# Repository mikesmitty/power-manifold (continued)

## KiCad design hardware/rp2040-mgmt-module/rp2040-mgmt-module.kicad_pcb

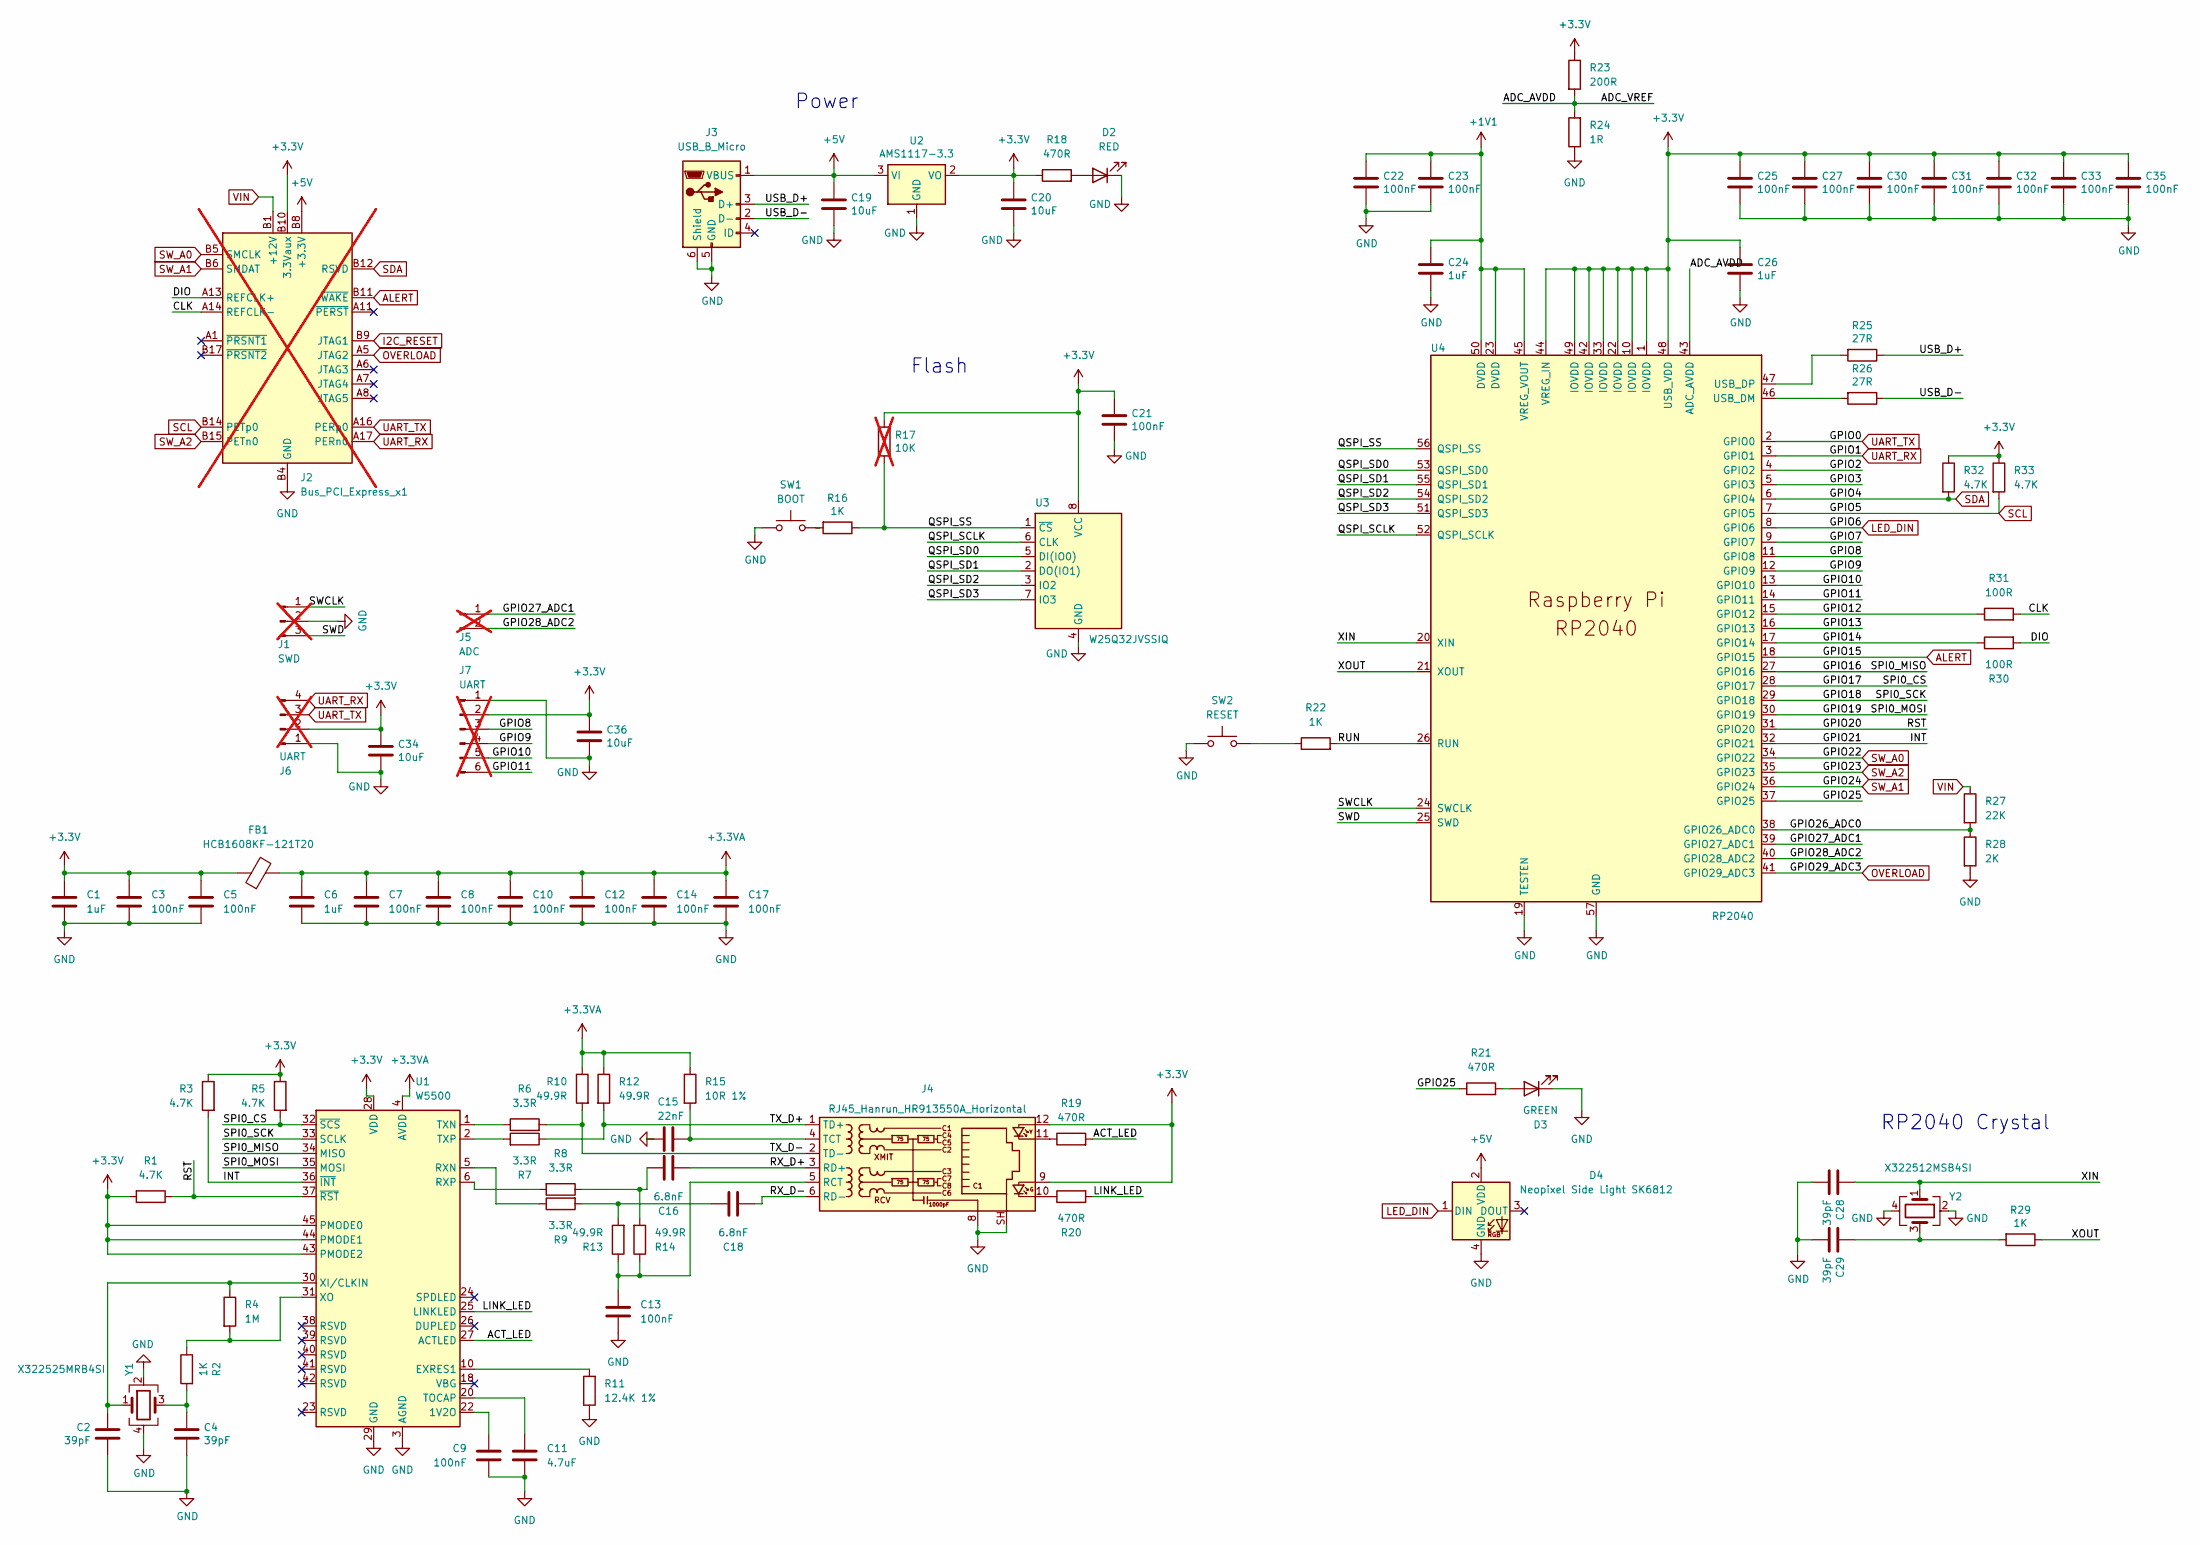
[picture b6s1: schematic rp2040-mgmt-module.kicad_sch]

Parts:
C1, C6, C24, C26: 1uF; C_0402_1005Metric; LCSC C52923
C2, C4, C28, C29: 39pF; C_0402_1005Metric; LCSC C342946
C3, C5, C7, C8, C9, C10, C12, C13, C14, C17, C21, C22, C23, C25, C27, C30, C31, C32, C33, C35: 100nF; C_0402_1005Metric; LCSC C1525
C11: 4.7uF; C_0402_1005Metric; LCSC C23733
C15: 22nF; C_0402_1005Metric; LCSC C1532
C16, C18: 6.8nF; C_0402_1005Metric; LCSC C1542
C19, C20, C34, C36: 10uF; C_0402_1005Metric; LCSC C15525
D2: RED; LED_0603_1608Metric; LCSC C2286
D3: GREEN; LED_0603_1608Metric; LCSC C965804
D4: Neopixel Side Light SK6812; LED_Neopixel_Side_Light_SK6812; LCSC C5378721
FB1: HCB1608KF-121T20; L_0603_1608Metric; LCSC C127301
J1: SWD; PinSocket_1x03_P2.54mm_Vertical; not fitted
J2: Bus_PCI_Express_x1; BUS_PCIexpress_x1; not fitted
J3: USB_B_Micro; USB_Micro-B_XKB_U254-051T-4BH83-F1S; LCSC C319160
J4: RJ45_Hanrun_HR913550A_Horizontal; RJ45_Hanrun_HR911105A_Horizontal; LCSC C163507
J5: ADC; PinSocket_1x02_P2.54mm_Vertical; not fitted
J6: UART; PinHeader_1x04_P2.54mm_Vertical; not fitted
J7: UART; PinHeader_1x06_P2.54mm_Vertical; not fitted
R1, R3, R5, R32, R33: 4.7K; R_0402_1005Metric; LCSC C25900
R2, R16, R22, R29: 1K; R_0402_1005Metric; LCSC C11702
R4: 1M; R_0402_1005Metric; LCSC C26083
R6, R7, R8, R9: 3.3R; R_0402_1005Metric; LCSC C270612
R10, R12, R13, R14: 49.9R; R_0402_1005Metric; LCSC C25120
R11: 12.4K 1%; R_0402_1005Metric; LCSC C11692
R15: 10R 1%; R_0402_1005Metric; LCSC C25077
R17: 10K; R_0402_1005Metric; not fitted
R18, R19, R20, R21: 470R; R_0402_1005Metric; LCSC C25117
R23: 200R; R_0402_1005Metric; LCSC C25087
R24: 1R; R_0402_1005Metric; LCSC C25086
R25, R26: 27R; R_0402_1005Metric; LCSC C25100
R27: 22K; R_0402_1005Metric; LCSC C25768
R28: 2K; R_0402_1005Metric; LCSC C4109
R30, R31: 100R; R_0402_1005Metric; LCSC C25076
SW1: BOOT; XKB_TS-1101_SWITCH; LCSC C318938
SW2: RESET; XKB_TS-1101_SWITCH; LCSC C318938
U1: W5500; LQFP-48_7x7mm_P0.5mm; LCSC C32843
U2: AMS1117-3.3; SOT-223-3_TabPin2; LCSC C6186
U3: W25Q32JVSSIQ; SOIC-8_5.23x5.23mm_P1.27mm; LCSC C179173
U4: RP2040; QFN-56-1EP_7x7mm_P0.4mm_EP3.2x3.2mm; LCSC C2040
Y1: X322525MRB4SI; Crystal_SMD_3225-4Pin_3.2x2.5mm; LCSC C70593
Y2: X322512MSB4SI; Crystal_SMD_3225-4Pin_3.2x2.5mm; LCSC C9002

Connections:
+1V1: C22.1, C23.1, C24.1, U4.23 (DVDD), U4.45 (VREG_VOUT), U4.50 (DVDD)
+3.3V: C1.1, C3.1, C5.1, C20.1, C21.1, C25.1, C26.1, C27.1, C30.1, C31.1, C32.1, C33.1, C34.1, C35.1, C36.1, FB1.1, J2.B10 (3.3Vaux), J4.9, J4.12, J6.2, J7.2, R1.2, R3.1, R5.1, R17.1, R18.1, R23.1, R32.1, R33.1, U1.28 (VDD), U1.43 (PMODE2), U1.44 (PMODE1), U1.45 (PMODE0), U2.2 (VO), U3.8 (VCC), U4.1 (IOVDD), U4.10 (IOVDD), U4.22 (IOVDD), U4.33 (IOVDD), U4.42 (IOVDD), U4.44 (VREG_IN), U4.48 (USB_VDD), U4.49 (IOVDD)
+3.3VA: C6.1, C7.1, C8.1, C10.1, C12.1, C14.1, C17.1, FB1.2, R10.1, R12.1, R15.1, U1.4 (AVDD), U1.8 (AVDD), U1.11 (AVDD), U1.15 (AVDD), U1.17 (AVDD), U1.21 (AVDD)
+5V: C19.1, D4.2 (VDD), J2.A9 (+3.3V), J2.A10 (+3.3V), J2.B8 (+3.3V), J3.1 (VBUS), U2.3 (VI)
/ACT_LED: R19.2, U1.27 (ACTLED)
/ADC_AVDD: R23.2, R24.2, U4.43 (ADC_AVDD)
/CLK: J2.A14 (REFCLK-), R31.2
/DIO: J2.A13 (REFCLK+), R30.2
/GPIO2: U4.4 (GPIO2)
/GPIO3: U4.5 (GPIO3)
/GPIO7: U4.9 (GPIO7)
/GPIO8: J7.3, U4.11 (GPIO8)
/GPIO9: J7.4, U4.12 (GPIO9)
/GPIO10: J7.5, U4.13 (GPIO10)
/GPIO11: J7.6, U4.14 (GPIO11)
/GPIO12: R31.1, U4.15 (GPIO12)
/GPIO13: U4.16 (GPIO13)
/GPIO14: R30.1, U4.17 (GPIO14)
/GPIO16: U1.34 (MISO), U4.27 (GPIO16)
/GPIO17: R5.2, U1.32 (~SCS), U4.28 (GPIO17)
/GPIO18: U1.33 (SCLK), U4.29 (GPIO18)
/GPIO19: U1.35 (MOSI), U4.30 (GPIO19)
/GPIO20: R1.1, U1.37 (~RST), U4.31 (GPIO20)
/GPIO21: R3.2, U1.36 (~INT), U4.32 (GPIO21)
/GPIO25: R21.1, U4.37 (GPIO25)
/GPIO26_ADC0: R27.2, R28.1, U4.38 (GPIO26_ADC0)
/GPIO27_ADC1: J5.1, U4.39 (GPIO27_ADC1)
/GPIO28_ADC2: J5.2, U4.40 (GPIO28_ADC2)
/LINK_LED: R20.2, U1.25 (LINKLED)
/QSPI_SCLK: U3.6 (CLK), U4.52 (QSPI_SCLK)
/QSPI_SD0: U3.5 (DI(IO0)), U4.53 (QSPI_SD0)
/QSPI_SD1: U3.2 (DO(IO1)), U4.55 (QSPI_SD1)
/QSPI_SD2: U3.3 (IO2), U4.54 (QSPI_SD2)
/QSPI_SD3: U3.7 (IO3), U4.51 (QSPI_SD3)
/QSPI_SS: R16.1, R17.2, U3.1 (~CS), U4.56 (QSPI_SS)
/RUN: R22.2, U4.26 (RUN)
/RX_D+: C16.2, J4.3 (RD+)
/RX_D-: C18.2, J4.6 (RD-)
/SWCLK: J1.1, U4.24 (SWCLK)
/SWD: J1.3, U4.25 (SWD)
/TX_D+: J4.1 (TD+), R7.1, R12.2
/TX_D-: J4.2 (TD-), R6.2, R10.2
/USB_D+: J3.3 (D+), R25.1
/USB_D-: J3.2 (D-), R26.1
/XIN: C28.1, U4.20 (XIN), Y2.1
/XOUT: R29.1, U4.21 (XOUT)
ALERT: J2.B11 (~WAKE), U4.18 (GPIO15)
GND: C1.2, C2.2, C3.2, C4.2, C5.2, C6.2, C7.2, C8.2, C9.2, C10.2, C11.2, C12.2, C13.2, C14.2, C15.1, C17.2, C19.2, C20.2, C21.2, C22.2, C23.2, C24.2, C25.2, C26.2, C27.2, C28.2, C29.2, C30.2, C31.2, C32.2, C33.2, C34.2, C35.2, C36.2, D2.1 (K), D3.1 (K), D4.4 (GND), J1.2, J2.A4 (GND), J2.A12 (GND), J2.A15 (GND), J2.A18 (GND), J2.B4 (GND), J2.B7 (GND), J2.B13 (GND), J2.B16 (GND), J2.B18 (GND), J3.5 (GND), J3.6 (Shield), J4.8, J4.SH, J6.1, J7.1, R11.1, R24.1, R28.2, SW1.1, SW2.1, U1.3 (AGND), U1.9 (AGND), U1.14 (AGND), U1.16 (AGND), U1.19 (AGND), U1.29 (GND), U1.48 (AGND), U2.1 (GND), U3.4 (GND), U4.19 (TESTEN), U4.57 (GND), Y1.2, Y1.4, Y2.2, Y2.4
I2C_RESET: J2.B9 (JTAG1)
LED_DIN: D4.1 (DIN), U4.8 (GPIO6)
unnamed: C4.1, R2.2, Y1.3
unnamed: C16.1, R8.1, R14.2
unnamed: C18.1, R9.2, R13.2
unnamed: C29.1, R29.2, Y2.3
unnamed: D2.2 (A), R18.2
unnamed: D3.2 (A), R21.2
unnamed: J4.10, R20.1
unnamed: J4.11, R19.1
unnamed: C13.1, J4.5 (RCT), R13.1, R14.1
unnamed: C15.2, J4.4 (TCT), R15.2
unnamed: R16.2, SW1.2
unnamed: R22.1, SW2.2
unnamed: C9.1, U1.22 (1V2O)
unnamed: R11.2, U1.10 (EXRES1)
unnamed: R9.1, U1.5 (RXN)
unnamed: R8.2, U1.6 (RXP)
unnamed: C11.1, U1.20 (TOCAP)
unnamed: R6.1, U1.1 (TXN)
unnamed: R7.2, U1.2 (TXP)
unnamed: C2.1, R4.1, U1.30 (XI/CLKIN), Y1.1
unnamed: R2.1, R4.2, U1.31 (XO)
unnamed: R26.2, U4.46 (USB_DM)
unnamed: R25.2, U4.47 (USB_DP)
OVERLOAD: J2.A5 (JTAG2), U4.41 (GPIO29_ADC3)
SCL: J2.B14 (PETp0), R33.2, U4.7 (GPIO5)
SDA: J2.B12 (RSVD), R32.2, U4.6 (GPIO4)
SW_A0: J2.B5 (SMCLK), U4.34 (GPIO22)
SW_A1: J2.B6 (SMDAT), U4.36 (GPIO24)
SW_A2: J2.B15 (PETn0), U4.35 (GPIO23)
UART_RX: J2.A17 (PERn0), J6.4, U4.3 (GPIO1)
UART_TX: J2.A16 (PERp0), J6.3, U4.2 (GPIO0)
VIN: J2.A2 (+12V), J2.A3 (+12V), J2.B1 (+12V), J2.B2 (+12V), J2.B3 (+12V), R27.1

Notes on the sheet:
Power
Flash
RP2040 Crystal

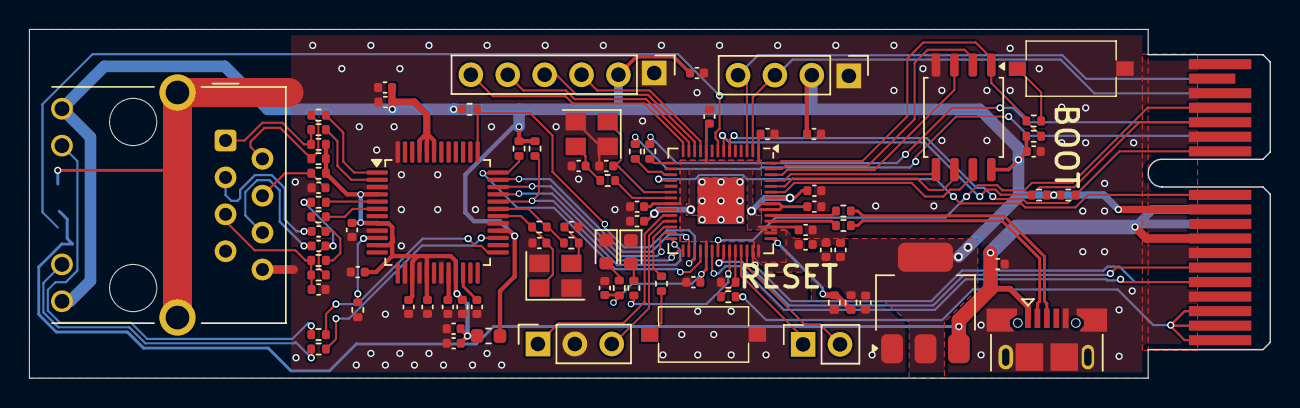
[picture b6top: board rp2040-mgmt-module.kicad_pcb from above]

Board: 2 copper layers, 85.4 x 24.0 mm, 88 parts (1 on the bottom side), 77 nets.

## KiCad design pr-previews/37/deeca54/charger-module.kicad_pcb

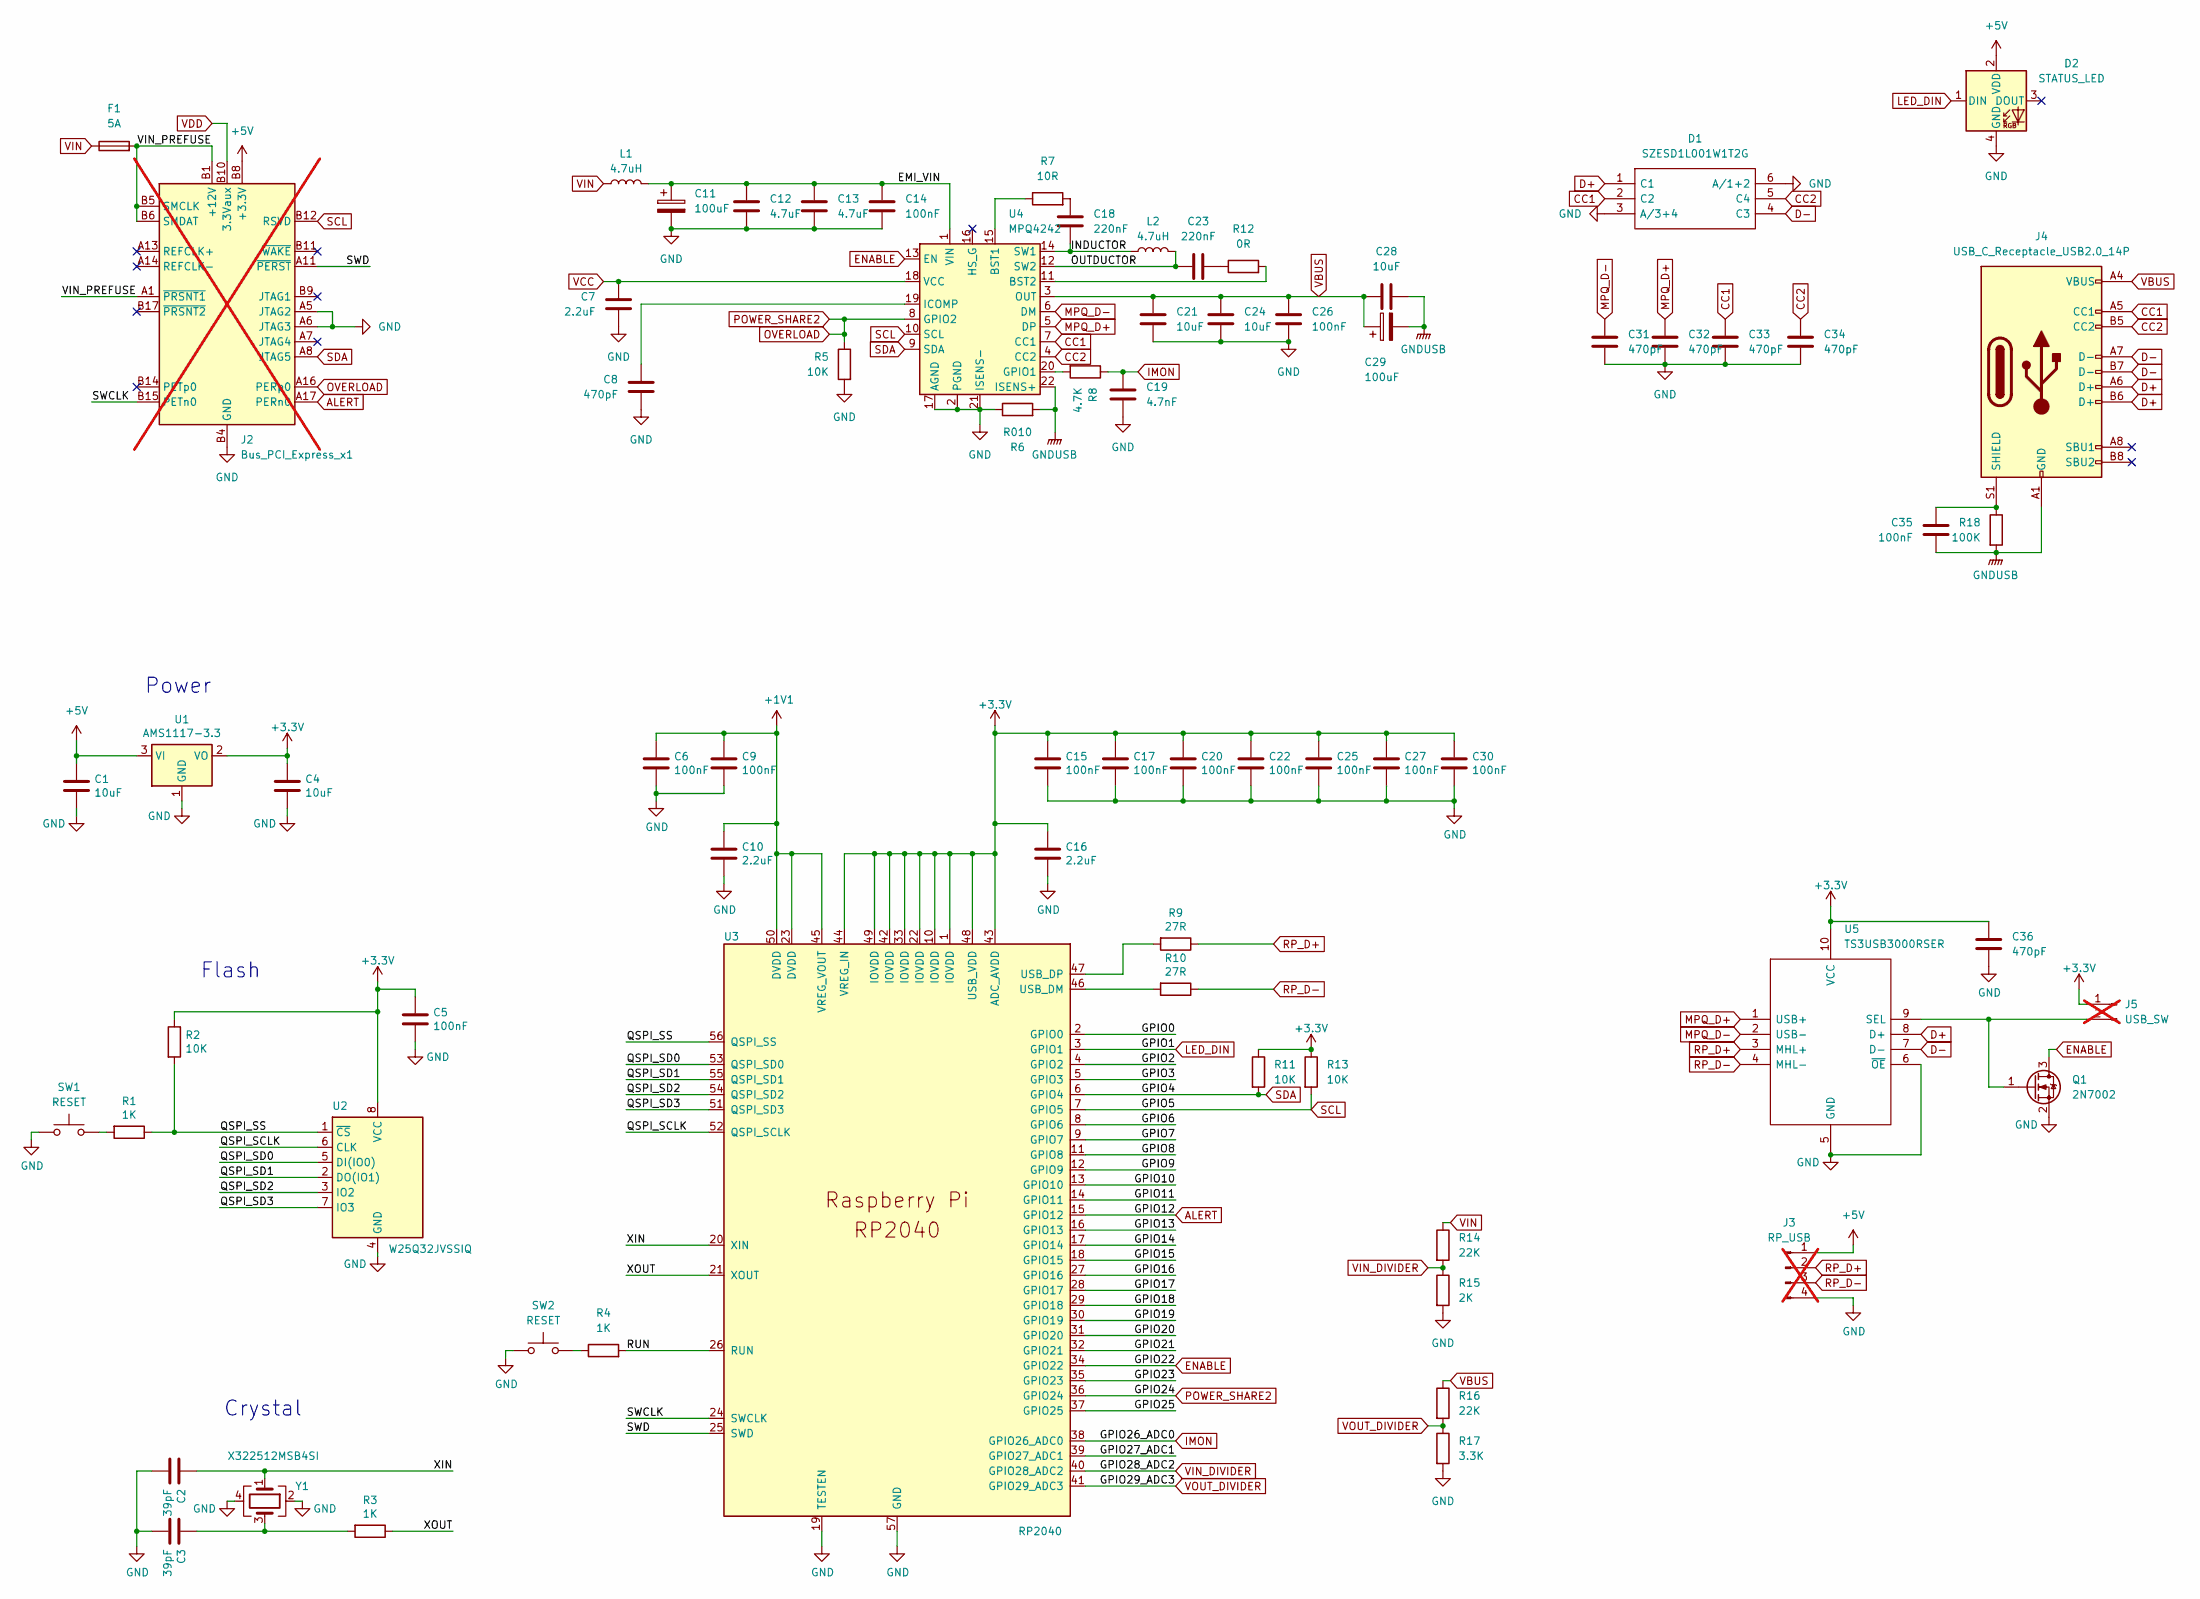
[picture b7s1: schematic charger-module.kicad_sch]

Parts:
C1, C4, C21, C24, C28: 10uF; C_0805_2012Metric; LCSC C15850
C2, C3: 39pF; C_0402_1005Metric; LCSC C106223
C5, C6, C9, C14, C15, C17, C20, C22, C25, C26, C27, C30, C35: 100nF; C_0402_1005Metric; LCSC C1525
C7, C10, C16: 2.2uF; C_0402_1005Metric; LCSC C12530
C8, C31, C32, C33, C34, C36: 470pF; C_0402_1005Metric; LCSC C1537
C11, C29: 100uF; CP_Elec_6.3x7.7; LCSC C3151829
C12, C13: 4.7uF; C_1206_3216Metric; LCSC C29823
C18, C23: 220nF; C_0603_1608Metric; LCSC C21120
C19: 4.7nF; C_0402_1005Metric; LCSC C1538
D1: SZESD1L001W1T2G; SOT65P210X110-6N; Mouser Part Number 863-SZESD1L001W1T2G
D2: STATUS_LED; LED_Neopixel_Side_Light_SK6812; LCSC C5378721
F1: 5A; Fuse_1206_3216Metric; LCSC C553937
J2: Bus_PCI_Express_x1; BUS_PCIexpress_x1; not fitted
J3: RP_USB; PinHeader_1x04_P2.54mm_Vertical; not fitted
J4: USB_C_Receptacle_USB2.0_14P; USB_C_Receptacle_XKB_U262-16XN-4BVC11; LCSC C2931474
J5: USB_SW; PinHeader_1x02_P2.54mm_Vertical; not fitted
L1, L2: 4.7uH; L_Sunlord_MWSA0603S; LCSC C408447
Q1: 2N7002; SOT-23; LCSC C8545
R1, R3, R4: 1K; R_0402_1005Metric; LCSC C11702
R2, R5, R11, R13: 10K; R_0402_1005Metric; LCSC C25744
R6: R010; R_2512_6332Metric; LCSC C127692
R7: 10R; R_0603_1608Metric; LCSC C22859
R8: 4.7K; R_0402_1005Metric; LCSC C25900
R9, R10: 27R; R_0603_1608Metric; LCSC C25190
R12: 0R; R_0603_1608Metric; LCSC C21189
R14, R16: 22K; R_0402_1005Metric; LCSC C25768
R15: 2K; R_0402_1005Metric; LCSC C4109
R17: 3.3K; R_0402_1005Metric; LCSC C25890
R18: 100K; R_0603_1608Metric; LCSC C25803
SW1, SW2: RESET; XKB_TS-1101_SWITCH; LCSC C318938
U1: AMS1117-3.3; SOT-223-3_TabPin2; LCSC C6186
U2: W25Q32JVSSIQ; SOIC-8_5.23x5.23mm_P1.27mm; LCSC C179173
U3: RP2040; QFN-56-1EP_7x7mm_P0.4mm_EP3.2x3.2mm; LCSC C2040
U4: MPQ4242; MPQ4242_QNF-22_4mmx5mm; LCSC C23268532
U5: TS3USB3000RSER; Mouser Part Number 595-TS3USB3000RSER
Y1: X322512MSB4SI; Crystal_SMD_3225-4Pin_3.2x2.5mm; LCSC C9002

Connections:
+1V1: C6.1, C9.1, C10.1, U3.23 (DVDD), U3.45 (VREG_VOUT), U3.50 (DVDD)
+3.3V: C4.1, C5.1, C15.1, C16.1, C17.1, C20.1, C22.1, C25.1, C27.1, C30.1, C36.1, J5.1, R2.1, R11.1, R13.1, U1.2 (VO), U2.8 (VCC), U3.1 (IOVDD), U3.10 (IOVDD), U3.22 (IOVDD), U3.33 (IOVDD), U3.42 (IOVDD), U3.43 (ADC_AVDD), U3.44 (VREG_IN), U3.48 (USB_VDD), U3.49 (IOVDD), U5.10 (VCC)
+5V: C1.1, D2.2 (VDD), J2.A9 (+3.3V), J2.A10 (+3.3V), J2.B8 (+3.3V), J3.1, U1.3 (VI)
/EMI_VIN: C11.1, C12.1, C13.1, C14.1, L1.2, U4.1 (VIN)
/GPIO0: U3.2 (GPIO0)
/GPIO2: U3.4 (GPIO2)
/GPIO3: U3.5 (GPIO3)
/GPIO6: U3.8 (GPIO6)
/GPIO7: U3.9 (GPIO7)
/GPIO8: U3.11 (GPIO8)
/GPIO9: U3.12 (GPIO9)
/GPIO10: U3.13 (GPIO10)
/GPIO11: U3.14 (GPIO11)
/GPIO13: U3.16 (GPIO13)
/GPIO14: U3.17 (GPIO14)
/GPIO15: U3.18 (GPIO15)
/GPIO16: U3.27 (GPIO16)
/GPIO17: U3.28 (GPIO17)
/GPIO18: U3.29 (GPIO18)
/GPIO19: U3.30 (GPIO19)
/GPIO20: U3.31 (GPIO20)
/GPIO21: U3.32 (GPIO21)
/GPIO23: U3.35 (GPIO23)
/GPIO25: U3.37 (GPIO25)
/GPIO27_ADC1: U3.39 (GPIO27_ADC1)
/INDUCTOR: C18.2, L2.1, U4.14 (SW1)
/OUTDUCTOR: C23.1, L2.2, U4.12 (SW2)
/QSPI_SCLK: U2.6 (CLK), U3.52 (QSPI_SCLK)
/QSPI_SD0: U2.5 (DI(IO0)), U3.53 (QSPI_SD0)
/QSPI_SD1: U2.2 (DO(IO1)), U3.55 (QSPI_SD1)
/QSPI_SD2: U2.3 (IO2), U3.54 (QSPI_SD2)
/QSPI_SD3: U2.7 (IO3), U3.51 (QSPI_SD3)
/QSPI_SS: R1.1, R2.2, U2.1 (~CS), U3.56 (QSPI_SS)
/RUN: R4.2, U3.26 (RUN)
/SWCLK: J2.B15 (PETn0), U3.24 (SWCLK)
/SWD: J2.A11 (~PERST), U3.25 (SWD)
/VIN_PREFUSE: F1.2, J2.A1 (~PRSNT1), J2.A2 (+12V), J2.A3 (+12V), J2.B1 (+12V), J2.B2 (+12V), J2.B3 (+12V), J2.B5 (SMCLK), J2.B6 (SMDAT)
/XIN: C2.1, U3.20 (XIN), Y1.1
/XOUT: R3.1, U3.21 (XOUT)
ALERT: J2.A17 (PERn0), U3.15 (GPIO12)
CC1: C33.1, D1.2 (C2), J4.A5 (CC1), U4.7 (CC1)
CC2: C34.1, D1.5 (C4), J4.B5 (CC2), U4.4 (CC2)
D+: D1.1 (C1), J4.A6 (D+), J4.B6 (D+), U5.8 (D+)
D-: D1.4 (C3), J4.A7 (D-), J4.B7 (D-), U5.7 (D-)
ENABLE: Q1.3 (D), U3.34 (GPIO22), U4.13 (EN)
GND: C1.2, C2.2, C3.2, C4.2, C5.2, C6.2, C7.2, C8.2, C9.2, C10.2, C11.2, C12.2, C13.2, C14.2, C15.2, C16.2, C17.2, C19.1, C20.2, C21.2, C22.2, C24.2, C25.2, C26.2, C27.2, C30.2, C31.2, C32.2, C33.2, C34.2, C36.2, D1.3 (A/3+4), D1.6 (A/1+2), D2.4 (GND), J2.A4 (GND), J2.A5 (JTAG2), J2.A6 (JTAG3), J2.A12 (GND), J2.A15 (GND), J2.A18 (GND), J2.B4 (GND), J2.B7 (GND), J2.B13 (GND), J2.B16 (GND), J2.B18 (GND), J3.4, Q1.2 (S), R5.2, R6.1, R15.2, R17.2, SW1.1, SW2.1, U1.1 (GND), U2.4 (GND), U3.19 (TESTEN), U3.57 (GND), U4.2 (PGND), U4.17 (AGND), U4.21 (ISENS-), U5.5 (GND), U5.6 (~OE), Y1.2, Y1.4
GNDUSB: C28.1, C29.2, C35.2, J4.A1 (GND), J4.A12 (GND), J4.B1 (GND), J4.B12 (GND), R6.2, R18.2, U4.22 (ISENS+)
IMON: C19.2, R8.1, U3.38 (GPIO26_ADC0)
LED_DIN: D2.1 (DIN), U3.3 (GPIO1)
MPQ_D+: C32.1, U4.5 (DP), U5.1 (USB+)
MPQ_D-: C31.1, U4.6 (DM), U5.2 (USB-)
unnamed: C3.1, R3.2, Y1.3
unnamed: C18.1, R7.2
unnamed: C23.2, R12.1
unnamed: C35.1, J4.S1 (SHIELD), R18.1
unnamed: J5.2, Q1.1 (G), U5.9 (SEL)
unnamed: R1.2, SW1.2
unnamed: R4.1, SW2.2
unnamed: R10.2, U3.46 (USB_DM)
unnamed: R9.2, U3.47 (USB_DP)
unnamed: R7.1, U4.15 (BST1)
unnamed: R12.2, U4.11 (BST2)
unnamed: R8.2, U4.20 (GPIO1)
unnamed: C8.1, U4.19 (ICOMP)
OVERLOAD: J2.A16 (PERp0), R5.1, U3.36 (GPIO24), U4.8 (GPIO2)
RP_D+: J3.2, R9.1, U5.3 (MHL+)
RP_D-: J3.3, R10.1, U5.4 (MHL-)
SCL: J2.B12 (RSVD), R13.2, U3.7 (GPIO5), U4.10 (SCL)
SDA: J2.A8 (JTAG5), R11.2, U3.6 (GPIO4), U4.9 (SDA)
VBUS: C21.1, C24.1, C26.1, C28.2, C29.1, J4.A4 (VBUS), J4.A9 (VBUS), J4.B4 (VBUS), J4.B9 (VBUS), R16.1, U4.3 (OUT)
VCC: C7.1, U4.18 (VCC)
VDD: J2.B10 (3.3Vaux)
VIN: F1.1, L1.1, R14.1
VIN_DIVIDER: R14.2, R15.1, U3.40 (GPIO28_ADC2)
VOUT_DIVIDER: R16.2, R17.1, U3.41 (GPIO29_ADC3)

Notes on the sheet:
Power
Crystal
Flash

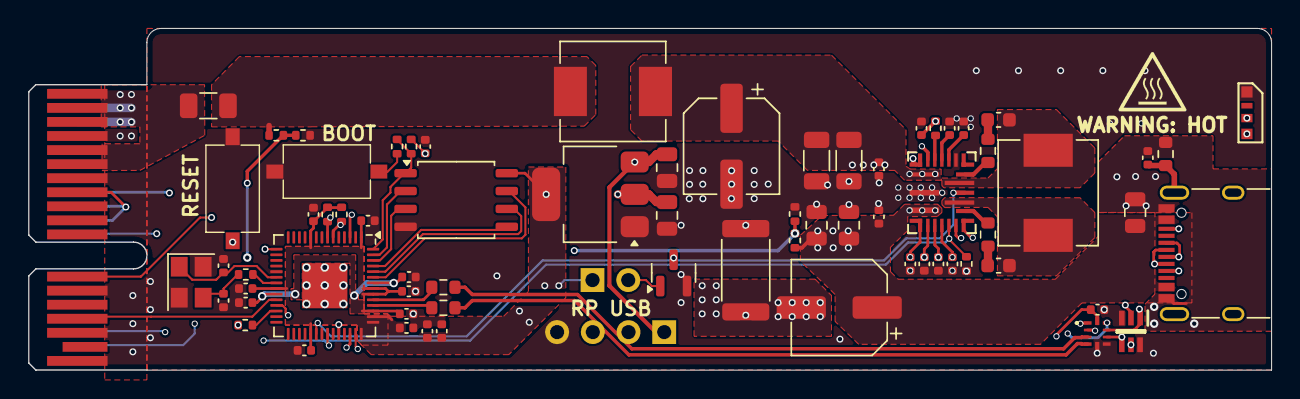
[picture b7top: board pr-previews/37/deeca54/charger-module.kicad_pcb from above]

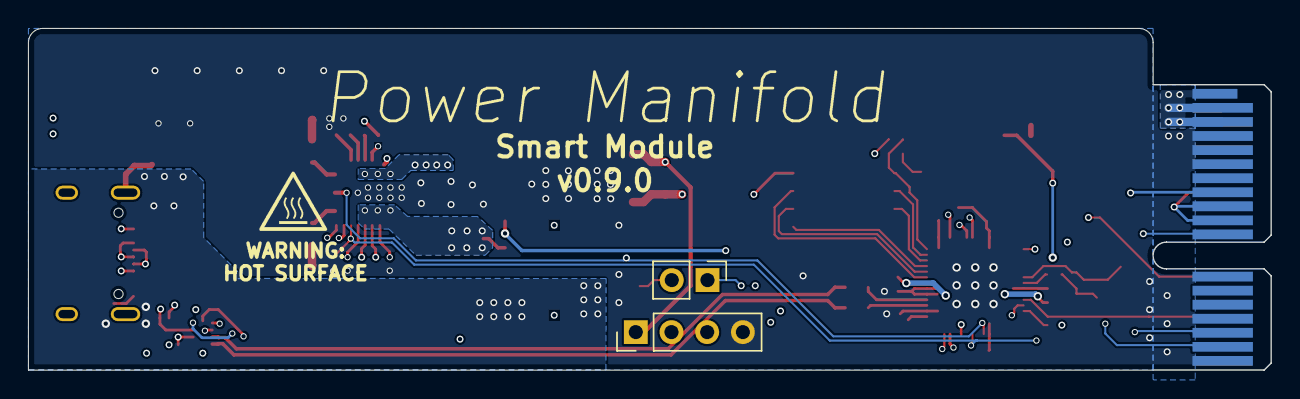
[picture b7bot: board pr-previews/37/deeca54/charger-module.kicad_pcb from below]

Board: 4 copper layers, 88.4 x 24.3 mm, 72 parts (2 on the bottom side), 53 nets.

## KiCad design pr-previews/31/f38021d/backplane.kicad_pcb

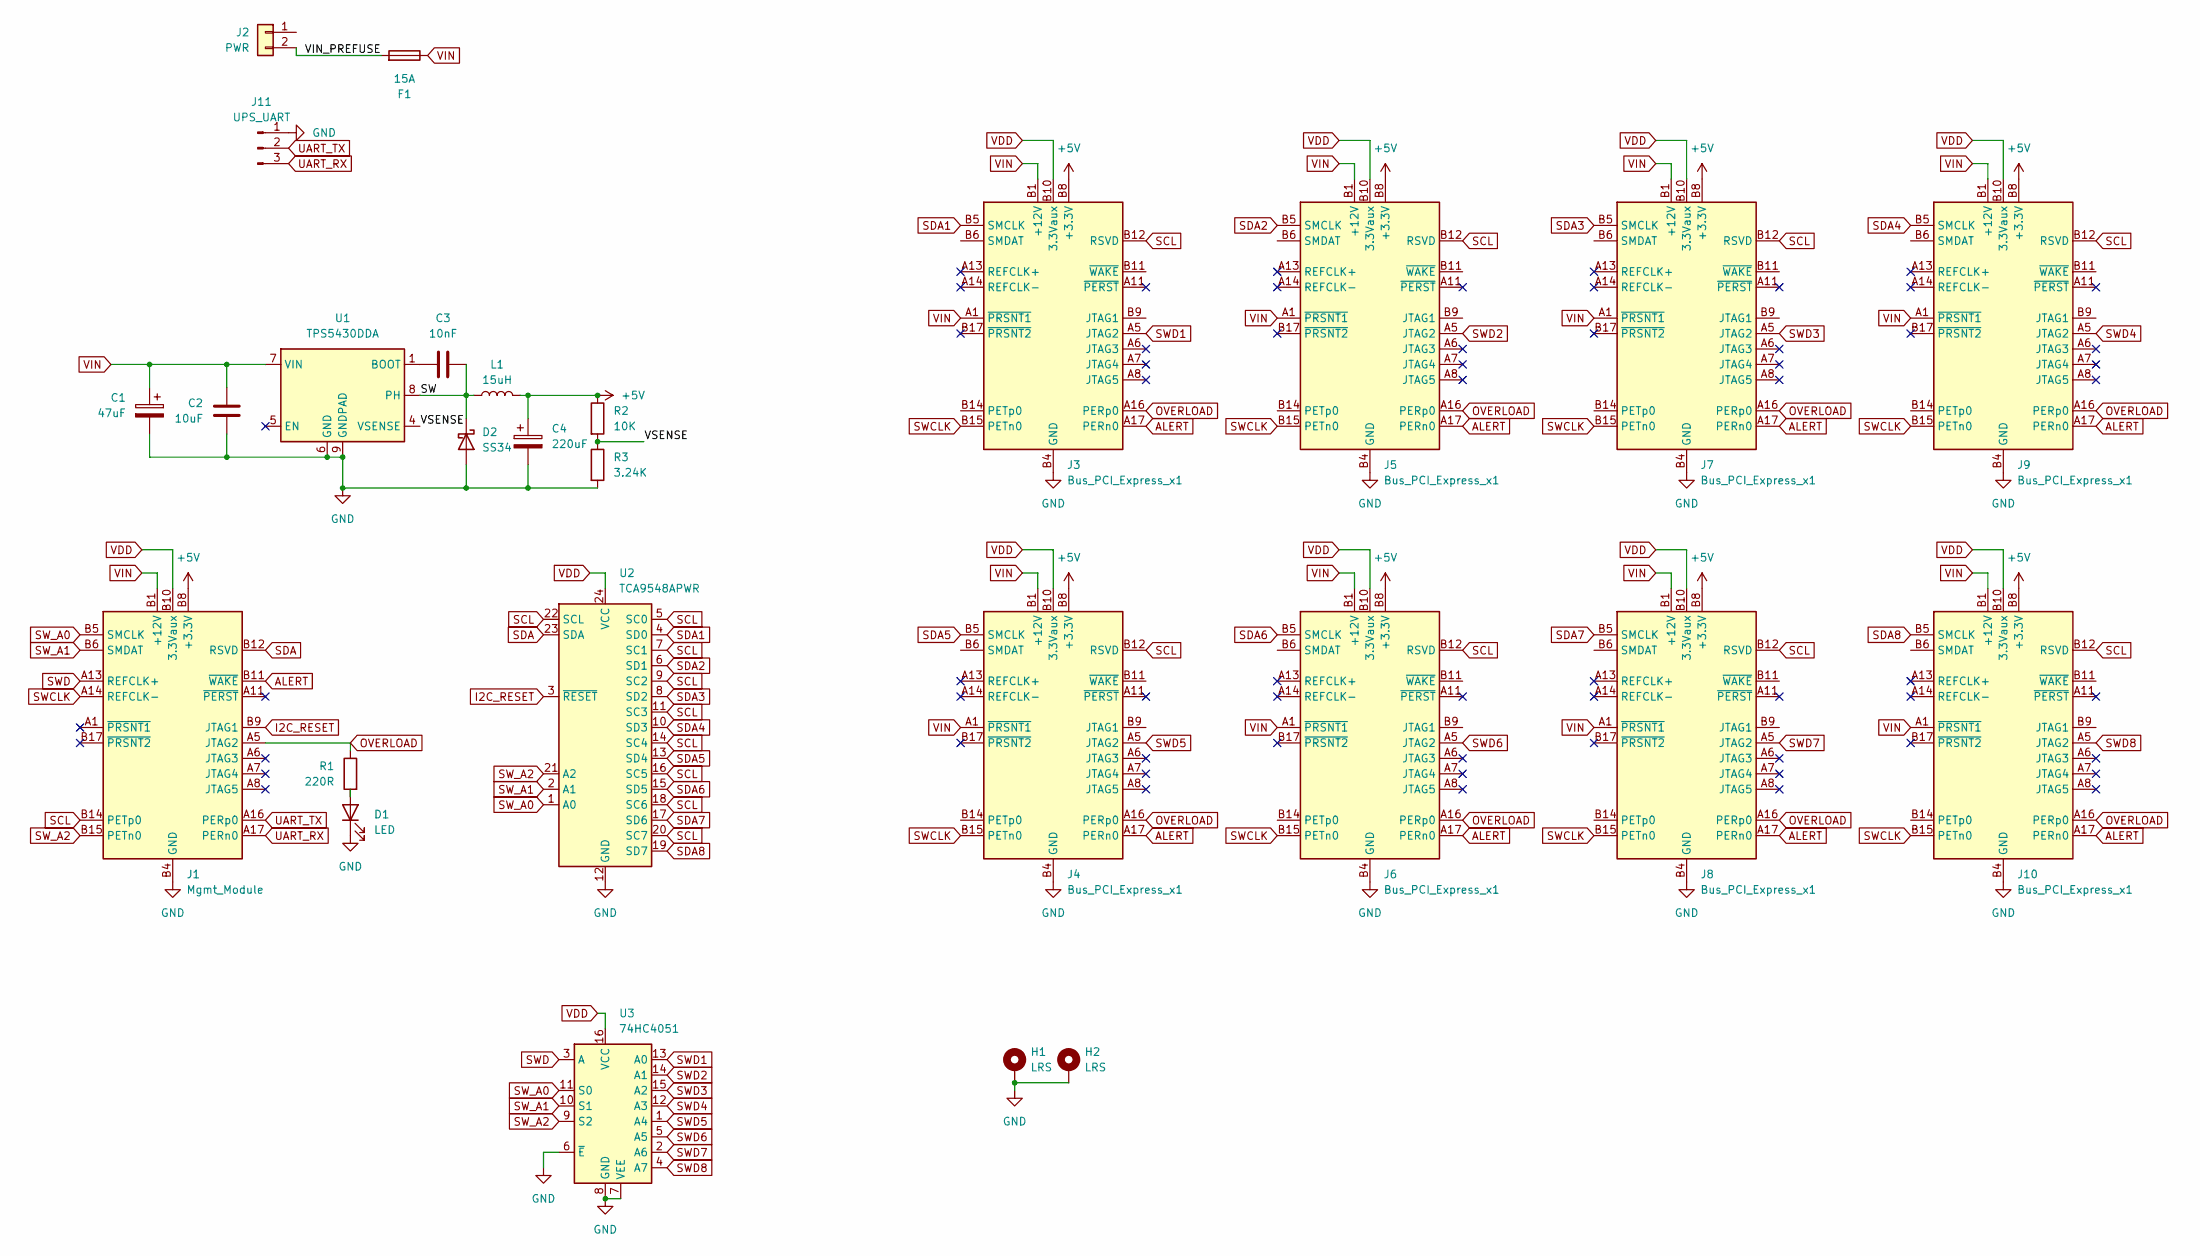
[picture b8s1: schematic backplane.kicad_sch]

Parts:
C1: 47uF; CP_Elec_6.3x7.7; LCSC C72523
C2: 10uF; C_1206_3216Metric; LCSC C13585
C3: 10nF; C_0603_1608Metric; LCSC C1589
C4: 220uF; CP_Elec_6.3x5.4_Nichicon; LCSC C72494
D1: LED; LED_0603_1608Metric; LCSC C2286
D2: SS34; D_SMA; LCSC C8678
F1: 15A; Fuseholder_Blade_Mini_Keystone_3568
H1, H2: LRS; MountingHole_4.3mm_M4_DIN965_Pad
J1: Mgmt_Module; AMPHENOL_PCI_E_10018783-10210TLF
J2: PWR; AMASS_XT30PW-M_1x02_P2.50mm_Horizontal; LCSC C431092
J3, J4, J5, J6, J7, J8, J9, J10: Bus_PCI_Express_x1; AMPHENOL_PCI_E_10018783-10210TLF
J11: UPS_UART; JST_XH_S3B-XH-A-1_1x03_P2.50mm_Horizontal
L1: 15uH; L_Sunlord_MWSA0603S; LCSC C408452
R1: 220R; R_0603_1608Metric; LCSC C22962
R2: 10K; R_0603_1608Metric; LCSC C25804
R3: 3.24K; R_0603_1608Metric; LCSC C22994
U1: TPS5430DDA; TI_SO-PowerPAD-8_ThermalVias; LCSC C9864
U2: TCA9548APWR; TSSOP-24_4.4x7.8mm_P0.65mm; LCSC C130026
U3: 74HC4051; TSSOP-16_4.4x5mm_P0.65mm; LCSC C5645

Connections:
+5V: C4.1, J1.A9 (+3.3V), J1.A10 (+3.3V), J1.B8 (+3.3V), J3.A9 (+3.3V), J3.A10 (+3.3V), J3.B8 (+3.3V), J4.A9 (+3.3V), J4.A10 (+3.3V), J4.B8 (+3.3V), J5.A9 (+3.3V), J5.A10 (+3.3V), J5.B8 (+3.3V), J6.A9 (+3.3V), J6.A10 (+3.3V), J6.B8 (+3.3V), J7.A9 (+3.3V), J7.A10 (+3.3V), J7.B8 (+3.3V), J8.A9 (+3.3V), J8.A10 (+3.3V), J8.B8 (+3.3V), J9.A9 (+3.3V), J9.A10 (+3.3V), J9.B8 (+3.3V), J10.A9 (+3.3V), J10.A10 (+3.3V), J10.B8 (+3.3V), L1.2, R2.1
/SW: C3.2, D2.1 (K), L1.1, U1.8 (PH)
/VIN_PREFUSE: F1.2, J2.2
/VSENSE: R2.2, R3.1, U1.4 (VSENSE)
ALERT: J1.B11 (~WAKE), J3.A17 (PERn0), J4.A17 (PERn0), J5.A17 (PERn0), J6.A17 (PERn0), J7.A17 (PERn0), J8.A17 (PERn0), J9.A17 (PERn0), J10.A17 (PERn0)
GND: C1.2, C2.2, C4.2, D1.1 (K), D2.2 (A), H1.1, H2.1, J1.A4 (GND), J1.A12 (GND), J1.A15 (GND), J1.A18 (GND), J1.B4 (GND), J1.B7 (GND), J1.B13 (GND), J1.B16 (GND), J1.B18 (GND), J3.A4 (GND), J3.A12 (GND), J3.A15 (GND), J3.A18 (GND), J3.B4 (GND), J3.B7 (GND), J3.B13 (GND), J3.B16 (GND), J3.B18 (GND), J4.A4 (GND), J4.A12 (GND), J4.A15 (GND), J4.A18 (GND), J4.B4 (GND), J4.B7 (GND), J4.B13 (GND), J4.B16 (GND), J4.B18 (GND), J5.A4 (GND), J5.A12 (GND), J5.A15 (GND), J5.A18 (GND), J5.B4 (GND), J5.B7 (GND), J5.B13 (GND), J5.B16 (GND), J5.B18 (GND), J6.A4 (GND), J6.A12 (GND), J6.A15 (GND), J6.A18 (GND), J6.B4 (GND), J6.B7 (GND), J6.B13 (GND), J6.B16 (GND), J6.B18 (GND), J7.A4 (GND), J7.A12 (GND), J7.A15 (GND), J7.A18 (GND), J7.B4 (GND), J7.B7 (GND), J7.B13 (GND), J7.B16 (GND), J7.B18 (GND), J8.A4 (GND), J8.A12 (GND), J8.A15 (GND), J8.A18 (GND), J8.B4 (GND), J8.B7 (GND), J8.B13 (GND), J8.B16 (GND), J8.B18 (GND), J9.A4 (GND), J9.A12 (GND), J9.A15 (GND), J9.A18 (GND), J9.B4 (GND), J9.B7 (GND), J9.B13 (GND), J9.B16 (GND), J9.B18 (GND), J10.A4 (GND), J10.A12 (GND), J10.A15 (GND), J10.A18 (GND), J10.B4 (GND), J10.B7 (GND), J10.B13 (GND), J10.B16 (GND), J10.B18 (GND), J11.1, R3.2, U1.6 (GND), U1.9 (GNDPAD), U2.12 (GND), U3.6 (~E), U3.7 (VEE), U3.8 (GND)
I2C_RESET: J1.B9 (JTAG1), U2.3 (~RESET)
unnamed: D1.2 (A), R1.2
unnamed: C3.1, U1.1 (BOOT)
OVERLOAD: J1.A5 (JTAG2), J3.A16 (PERp0), J4.A16 (PERp0), J5.A16 (PERp0), J6.A16 (PERp0), J7.A16 (PERp0), J8.A16 (PERp0), J9.A16 (PERp0), J10.A16 (PERp0), R1.1
SCL: J1.B14 (PETp0), J3.B12 (RSVD), J4.B12 (RSVD), J5.B12 (RSVD), J6.B12 (RSVD), J7.B12 (RSVD), J8.B12 (RSVD), J9.B12 (RSVD), J10.B12 (RSVD), U2.5 (SC0), U2.7 (SC1), U2.9 (SC2), U2.11 (SC3), U2.14 (SC4), U2.16 (SC5), U2.18 (SC6), U2.20 (SC7), U2.22 (SCL)
SDA: J1.B12 (RSVD), U2.23 (SDA)
SDA1: J3.B5 (SMCLK), U2.4 (SD0)
SDA2: J5.B5 (SMCLK), U2.6 (SD1)
SDA3: J7.B5 (SMCLK), U2.8 (SD2)
SDA4: J9.B5 (SMCLK), U2.10 (SD3)
SDA5: J4.B5 (SMCLK), U2.13 (SD4)
SDA6: J6.B5 (SMCLK), U2.15 (SD5)
SDA7: J8.B5 (SMCLK), U2.17 (SD6)
SDA8: J10.B5 (SMCLK), U2.19 (SD7)
SWCLK: J1.A14 (REFCLK-), J3.B15 (PETn0), J4.B15 (PETn0), J5.B15 (PETn0), J6.B15 (PETn0), J7.B15 (PETn0), J8.B15 (PETn0), J9.B15 (PETn0), J10.B15 (PETn0)
SWD: J1.A13 (REFCLK+), U3.3 (A)
SWD1: J3.A5 (JTAG2), U3.13 (A0)
SWD2: J5.A5 (JTAG2), U3.14 (A1)
SWD3: J7.A5 (JTAG2), U3.15 (A2)
SWD4: J9.A5 (JTAG2), U3.12 (A3)
SWD5: J4.A5 (JTAG2), U3.1 (A4)
SWD6: J6.A5 (JTAG2), U3.5 (A5)
SWD7: J8.A5 (JTAG2), U3.2 (A6)
SWD8: J10.A5 (JTAG2), U3.4 (A7)
SW_A0: J1.B5 (SMCLK), U2.1 (A0), U3.11 (S0)
SW_A1: J1.B6 (SMDAT), U2.2 (A1), U3.10 (S1)
SW_A2: J1.B15 (PETn0), U2.21 (A2), U3.9 (S2)
UART_RX: J1.A17 (PERn0), J11.3
UART_TX: J1.A16 (PERp0), J11.2
VDD: J1.B10 (3.3Vaux), J3.B10 (3.3Vaux), J4.B10 (3.3Vaux), J5.B10 (3.3Vaux), J6.B10 (3.3Vaux), J7.B10 (3.3Vaux), J8.B10 (3.3Vaux), J9.B10 (3.3Vaux), J10.B10 (3.3Vaux), U2.24 (VCC), U3.16 (VCC)
VIN: C1.1, C2.1, F1.1, J1.A2 (+12V), J1.A3 (+12V), J1.B1 (+12V), J1.B2 (+12V), J1.B3 (+12V), J3.A1 (~PRSNT1), J3.A2 (+12V), J3.A3 (+12V), J3.B1 (+12V), J3.B2 (+12V), J3.B3 (+12V), J4.A1 (~PRSNT1), J4.A2 (+12V), J4.A3 (+12V), J4.B1 (+12V), J4.B2 (+12V), J4.B3 (+12V), J5.A1 (~PRSNT1), J5.A2 (+12V), J5.A3 (+12V), J5.B1 (+12V), J5.B2 (+12V), J5.B3 (+12V), J6.A1 (~PRSNT1), J6.A2 (+12V), J6.A3 (+12V), J6.B1 (+12V), J6.B2 (+12V), J6.B3 (+12V), J7.A1 (~PRSNT1), J7.A2 (+12V), J7.A3 (+12V), J7.B1 (+12V), J7.B2 (+12V), J7.B3 (+12V), J8.A1 (~PRSNT1), J8.A2 (+12V), J8.A3 (+12V), J8.B1 (+12V), J8.B2 (+12V), J8.B3 (+12V), J9.A1 (~PRSNT1), J9.A2 (+12V), J9.A3 (+12V), J9.B1 (+12V), J9.B2 (+12V), J9.B3 (+12V), J10.A1 (~PRSNT1), J10.A2 (+12V), J10.A3 (+12V), J10.B1 (+12V), J10.B2 (+12V), J10.B3 (+12V), U1.7 (VIN)

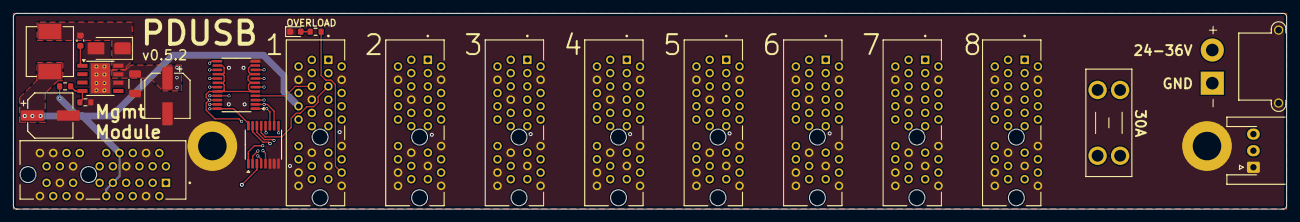
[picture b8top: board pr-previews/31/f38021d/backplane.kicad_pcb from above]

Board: 4 copper layers, 192.0 x 29.5 mm, 27 parts (0 on the bottom side), 37 nets.
